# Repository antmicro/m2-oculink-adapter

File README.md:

# M.2 to OCuLink Adapter

Copyright (c) 2025 [Antmicro](https://www.antmicro.com)

## Overview

This project includes PCB design files that define a simple M.2 (M-key) to OCuLink adapter.
It can be used for connecting the on-board PCIe M.2 slots with remote PCIe devices via OCuLink cables. 
This board has been designed to be compatible with Antmicro's [Jetson Orin Baseboard](https://github.com/antmicro/jetson-orin-baseboard).

If you plan to use it with other pieces of hardware, please inspect the schematics and connection diagrams beforehand. 
The PCB design files were prepared in KiCad 9.x.

## Key features

- Compatible with Antmicro's Jetson Orin Baseboard
- Exposes 4 lanes of PCIe via an OCuLink connector
- M.2 (M-key)
- OCuLink connector (Amphenol G14A421211112HR)
- Compatible with 2280, 2260, 2242 M.2 mechanical form factors

## License

This project is licensed under the [Apache-2.0](LICENSE) license.

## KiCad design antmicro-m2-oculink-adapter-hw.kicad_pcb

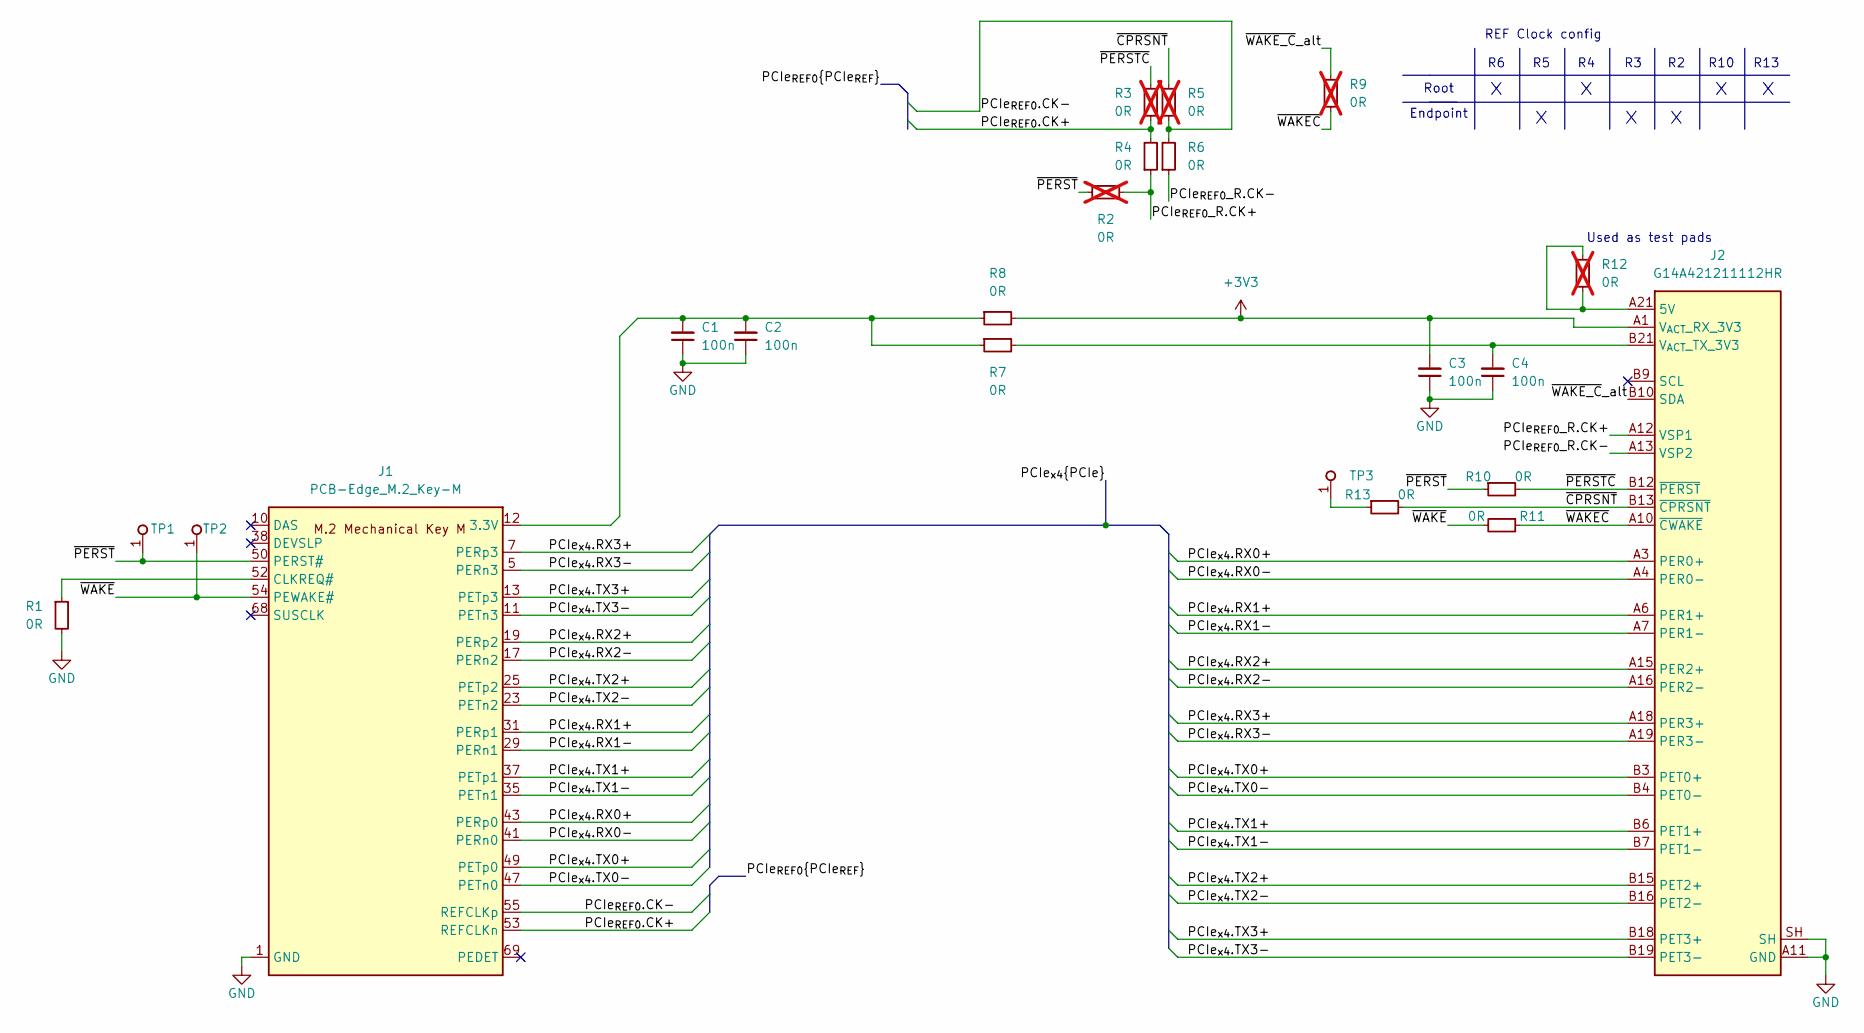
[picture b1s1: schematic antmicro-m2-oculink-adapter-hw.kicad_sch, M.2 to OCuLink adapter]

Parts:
C1, C2, C3, C4: C_100n_16V_X7R_0402; C_0402_1005Metric; Voltage 16V; MPN C0402C104J4RAC7411
J1: PCB-Edge_M.2_Key-M
J2: OCuLink_x4_Amphenol_G14A421211112HR; Amphenol_G14A421211112HR; MPN G14A421211112HR
R1, R7, R8, R11: R_0R_0402; R_0402_1005Metric; MPN ERJ2GE0R00X
R2, R3, R5, R9: R_0R_0201; R_0201; Tolerance 1%; MPN CR0201-FX-0R00GLF; not fitted
R4, R6, R10, R13: R_0R_0201; R_0201; Tolerance 1%; MPN CR0201-FX-0R00GLF
R12: R_0R_0402; R_0402_1005Metric; MPN ERJ2GE0R00X; not fitted
TP1, TP2: TP_1.5mm_SMD; TP_SMD_1.5mm
TP3: TP_1mm_SMD; TP_SMD_1mm

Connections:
+3V3: C3.2, J2.A1 (V_{ACT}_RX_3V3), R8.2
/PCIe_{REF0}.CK+: J1.53 (REFCLKn), R3.1, R4.2
/PCIe_{REF0}.CK-: J1.55 (REFCLKp), R5.1, R6.2
/PCIe_{REF0}_R.CK+: J2.A12 (VSP1), R2.1, R4.1
/PCIe_{REF0}_R.CK-: J2.A13 (VSP2), R6.1
/PCIe_{x4}.RX0+: J1.43 (PERp0), J2.A3 (PER0+)
/PCIe_{x4}.RX0-: J1.41 (PERn0), J2.A4 (PER0-)
/PCIe_{x4}.RX1+: J1.31 (PERp1), J2.A6 (PER1+)
/PCIe_{x4}.RX1-: J1.29 (PERn1), J2.A7 (PER1-)
/PCIe_{x4}.RX2+: J1.19 (PERp2), J2.A15 (PER2+)
/PCIe_{x4}.RX2-: J1.17 (PERn2), J2.A16 (PER2-)
/PCIe_{x4}.RX3+: J1.7 (PERp3), J2.A18 (PER3+)
/PCIe_{x4}.RX3-: J1.5 (PERn3), J2.A19 (PER3-)
/PCIe_{x4}.TX0+: J1.49 (PETp0), J2.B3 (PET0+)
/PCIe_{x4}.TX0-: J1.47 (PETn0), J2.B4 (PET0-)
/PCIe_{x4}.TX1+: J1.37 (PETp1), J2.B6 (PET1+)
/PCIe_{x4}.TX1-: J1.35 (PETn1), J2.B7 (PET1-)
/PCIe_{x4}.TX2+: J1.25 (PETp2), J2.B15 (PET2+)
/PCIe_{x4}.TX2-: J1.23 (PETn2), J2.B16 (PET2-)
/PCIe_{x4}.TX3+: J1.13 (PETp3), J2.B18 (PET3+)
/PCIe_{x4}.TX3-: J1.11 (PETn3), J2.B19 (PET3-)
/~CPRSNT: J2.B13 (~CPRSNT), R5.2, R13.2
/~PERSTC: J2.B12 (~PERST), R3.2, R10.2
/~PERST: J1.50 (PERST#), R2.2, R10.1, TP1.1
/~WAKEC: J2.A10 (~CWAKE), R9.1, R11.1
/~WAKE_C_alt: J2.B10 (SDA), R9.2
/~WAKE: J1.54 (PEWAKE#), R11.2, TP2.1
GND: C1.1, C2.1, C3.1, C4.1, J1.1 (GND), J1.3 (GND), J1.9 (GND), J1.15 (GND), J1.21 (GND), J1.27 (GND), J1.33 (GND), J1.39 (GND), J1.45 (GND), J1.51 (GND), J1.57 (GND), J1.71 (GND), J1.73 (GND), J1.75 (GND), J2.A2 (GND), J2.A5 (GND), J2.A8 (GND), J2.A11 (GND), J2.A14 (GND), J2.A17 (GND), J2.A20 (GND), J2.B2 (GND), J2.B5 (GND), J2.B8 (GND), J2.B11 (GND), J2.B14 (GND), J2.B17 (GND), J2.B20 (GND), J2.SH, R1.2
unnamed: C1.2, C2.2, J1.2 (3.3V), J1.4 (3.3V), J1.12 (3.3V), J1.14 (3.3V), J1.16 (3.3V), J1.18 (3.3V), J1.70 (3.3V), J1.72 (3.3V), J1.74 (3.3V), R7.1, R8.1
unnamed: J1.52 (CLKREQ#), R1.1
unnamed: J2.A21 (5V), J2.B1 (5V), R12.1, R12.2
unnamed: C4.2, J2.B21 (V_{ACT}_TX_3V3), R7.2
unnamed: R13.1, TP3.1

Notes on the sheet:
REF Clock config
Endpoint
Root
Used as test pads
R13
R10

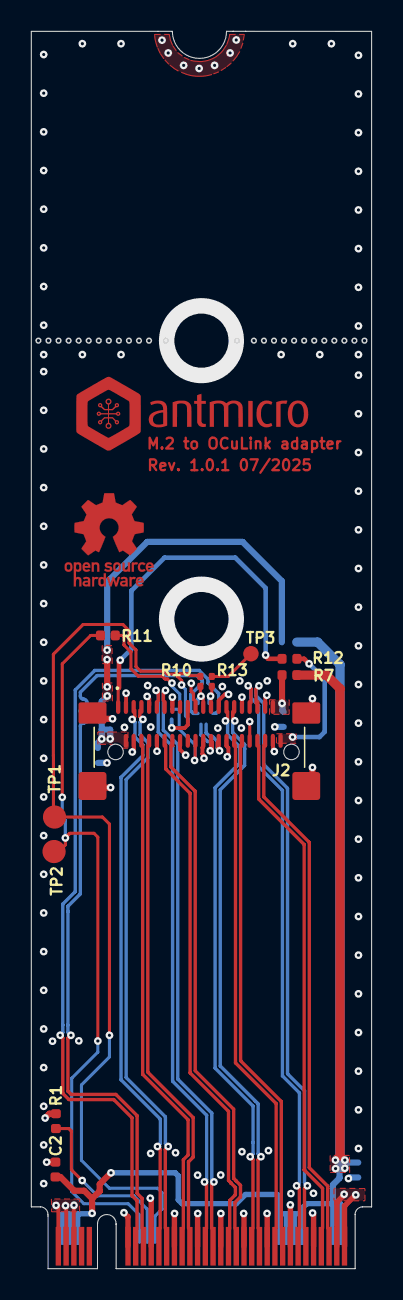
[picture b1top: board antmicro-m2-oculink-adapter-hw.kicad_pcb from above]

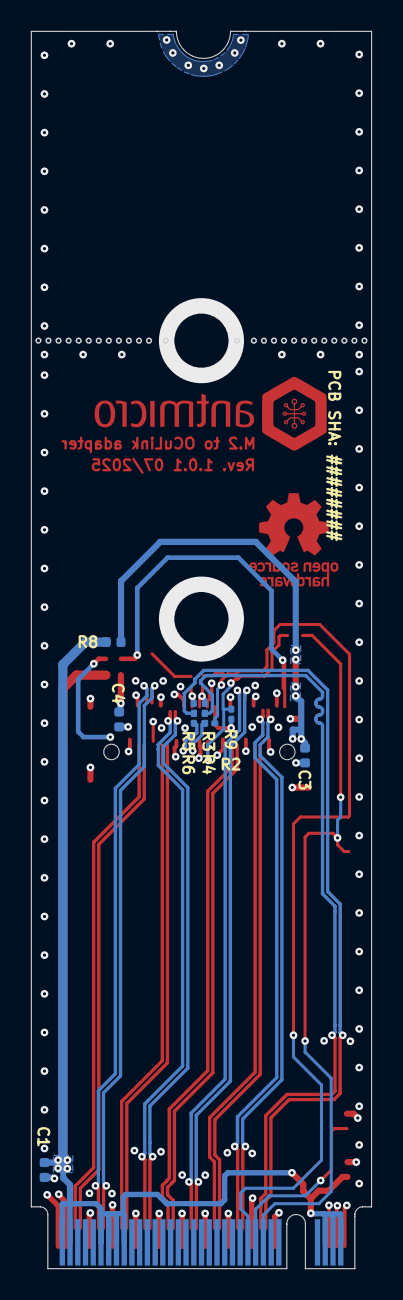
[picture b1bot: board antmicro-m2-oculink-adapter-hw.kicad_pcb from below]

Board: 4 copper layers, 22.0 x 80.0 mm, 22 parts (10 on the bottom side), 33 nets.

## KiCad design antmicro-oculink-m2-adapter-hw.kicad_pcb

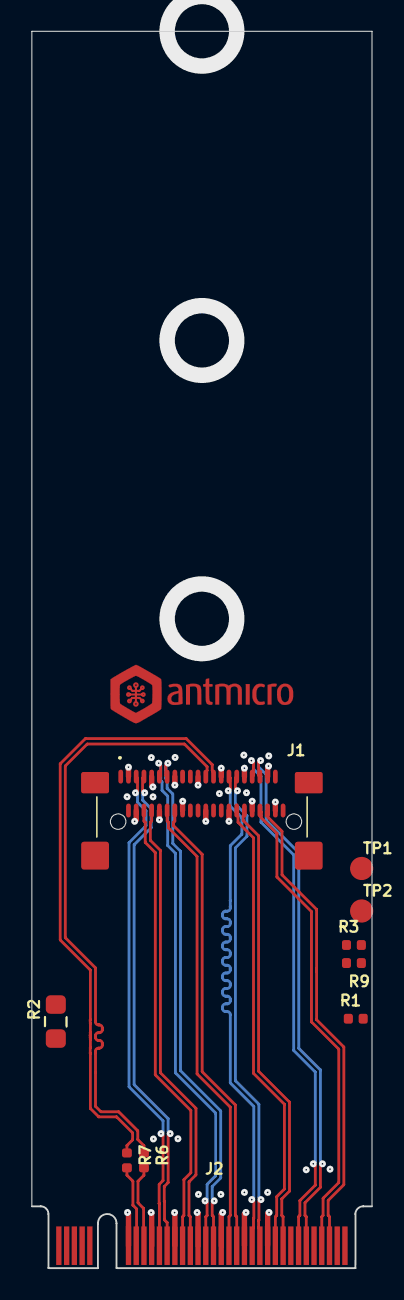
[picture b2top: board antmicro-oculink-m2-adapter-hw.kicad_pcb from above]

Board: 4 copper layers, 22.0 x 80.0 mm, 10 parts (0 on the bottom side), 28 nets.

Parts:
J1: OCuLink_x4_Amphenol_G14A421211112HR; Amphenol_G14A421211112HR
J2: PCB-Edge_M.2_Key-M
R1, R3, R6, R7, R9: R_0R_0402; R_0402_1005Metric
R2: R_0R_0805; R_0805_2012Metric
TP1, TP2: TP_1.5mm_SMD; TP_SMD_1.5mm

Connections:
+3V3: J1.A21 (V_{ACT}_TX_3V3), J1.B1 (V_{ACT}_RX_3V3), R2.2
/PCIe_{REF0}.CK+: J2.55 (REFCLKp), R7.2
/PCIe_{REF0}.CK-: J2.53 (REFCLKn), R6.2
/PCIe_{REF0}_R.CK+: J1.B13 (VSP2), R7.1
/PCIe_{REF0}_R.CK-: J1.B12 (VSP1), R6.1
/PCIe_{x4}.RX0+: J1.B3 (PER0+), J2.49 (SATA-A+)
/PCIe_{x4}.RX0-: J1.B4 (PER0-), J2.47 (SATA-A-)
/PCIe_{x4}.RX1+: J1.B6 (PER1+), J2.37 (PETp1)
/PCIe_{x4}.RX1-: J1.B7 (PER1-), J2.35 (PETn1)
/PCIe_{x4}.RX2+: J1.B15 (PER2+), J2.25 (PETp2)
/PCIe_{x4}.RX2-: J1.B16 (PER2-), J2.23 (PETn2)
/PCIe_{x4}.RX3+: J1.B18 (PER3+), J2.13 (PETp3)
/PCIe_{x4}.RX3-: J1.B19 (PER3-), J2.11 (PETn3)
/PCIe_{x4}.TX0+: J1.A3 (PET0+), J2.43 (SATA-B+)
/PCIe_{x4}.TX0-: J1.A4 (PET0-), J2.41 (SATA-B-)
/PCIe_{x4}.TX1+: J1.A6 (PET1+), J2.31 (PERp1)
/PCIe_{x4}.TX1-: J1.A7 (PET1-), J2.29 (PERn1)
/PCIe_{x4}.TX2+: J1.A15 (PET2+), J2.19 (PERp2)
/PCIe_{x4}.TX2-: J1.A16 (PET2-), J2.17 (PERn2)
/PCIe_{x4}.TX3+: J1.A18 (PET3+), J2.7 (PERp3)
/PCIe_{x4}.TX3-: J1.A19 (PET3-), J2.5 (PERn3)
/~PERSTC: J1.A12 (~PERST), R1.1
/~PERST: J2.50 (PERST#), R1.2, TP1.1
/~WAKEC: J1.B10 (~CWAKE), R3.1
/~WAKE: J2.54 (PEWAKE#), R3.2, TP2.1
GND: J1.A2 (GND), J1.A5 (GND), J1.A8 (GND), J1.A11 (GND), J1.A14 (GND), J1.A17 (GND), J1.A20 (GND), J1.B2 (GND), J1.B5 (GND), J1.B8 (GND), J1.B11 (GND), J1.B14 (GND), J1.B17 (GND), J1.B20 (GND), J1.SH, J2.1 (GND), J2.3 (GND), J2.9 (GND), J2.15 (GND), J2.21 (GND), J2.27 (GND), J2.33 (GND), J2.39 (GND), J2.45 (GND), J2.51 (GND), J2.57 (GND), J2.71 (GND), J2.73 (GND), J2.75 (GND), R9.2
unnamed: J2.2 (3.3V), J2.4 (3.3V), J2.12 (3.3V), J2.14 (3.3V), J2.16 (3.3V), J2.18 (3.3V), J2.70 (3.3V), J2.72 (3.3V), J2.74 (3.3V), R2.1
unnamed: J2.52 (CLKREQ#), R9.1

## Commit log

2025-07-09 [#79281] Inital commit
2025-07-24 [#80280] Add LICENSE
2025-07-24 [#79281] Update key features in README
2025-07-24 [#79281] add README.md
2025-07-24 [#79281] Add ci.yml, initial connector placement
2025-07-24 [#79281] Connector placement and PCIe routing
2025-07-24 [#79281] Add .gitignore and remove kicad_prl file
2025-07-24 [#79281] Remove unnecessary text on schematic
2025-07-24 [#79281] Fix lane polarity
2025-07-24 [#79281] Clean up gnd vias and pcie routing
2025-07-24 [#79281] Rename files, Fix net class naming, Undo crossover on PCIe lanes, change OCulink symbol to host side version
2025-07-24 [#79281] Remove old files
2025-07-24 [#79281] Place 0R resistors and test points
2025-07-24 [#80280] Add mouse bites
2025-07-24 [#79281] Fix schematic annotation
2025-07-24 [#79281] Change 0R sizing, add OSHW logo, route 3.3V rail and control signals
2025-07-24 [#80280] Fix DRC
2025-07-24 [#80280] Round diff pairs. Move logo to 2 segment and make more room for the OCulink cable
2025-07-24 [#80280] CI test
2025-07-24 [#80280] Add PCB SHA string
2025-07-24 [#80280] Move edge cuts from footprints
2025-07-24 [#80280] Workaround kicad bug
2025-07-24 [#80280] Modify edge drill hole to use pad instead of filled polygon
2025-07-24 [#80280] Rename edge drill hole, fix drc
2025-07-24 [#80280] Add User 9 layer
2025-07-24 [#80280] Clean up tracks, change gnd cutout size, fix drc errors, add more vias, move antmicro logo, change text size
2025-07-24 [#80280] Cleanup tracks
2025-07-24 [#80747] Add license info to README
2025-07-24 [#80747] Add render to README
2025-07-24 [#80747] Update testpoint info in README
2025-07-24 [#80747] Clean up tracks
2025-07-24 [#80747] change antmicro logo and correct date format
2025-07-24 [#80747] Fix DRC
2025-07-24 [#80747] Replace edge drill footprint
2025-07-24 [#80747] Kmake bug workaround
2025-07-24 [#80747] Update README
2025-07-24 [#80747] Remove soldermask from drill opening
2025-07-24 [#80747] Update render
2025-07-24 [#80747] Change drill hole size to 3.5mm
2025-07-24 README: update description, resize render
2025-07-24 README: Fix name
2025-07-24 minor text refinement
2025-07-24 further language review
2025-07-24 minor fixes
2025-07-24 the ceremonial unification of the M-key
2025-07-25 [#80997] Fix stack-up
2025-07-28 [#81030] Rotate sha
2025-07-28 [#81030] Change OCulink connector pad size to 0.28mm
2025-07-31 [#81131] Change resistor, testpoint sizing. Add 0R to 3V3 and ~CWAKE
2025-07-31 [#81131] Add 0R selector for refclk
2025-07-31 [#81131] Cleanup tracks
2025-07-31 [#81131] Clean up drc
2025-07-31 [#81131] Fix meander add gnd connections
2025-07-31 [#81131] Fix vias, zones
2025-07-31 [#81131] Fix schematic 3V3
2025-07-31 [#81131] Clean drc
2025-07-31 [#81131] Clean-up tracks, shorten stubs, relocate R1, align silkscreen
2025-07-31 [#81131] Add 0R on 5V, Clean drc
2025-08-01 [#81131] Increase silkscreen spacing, add gnd cutouts to vias, increase distance drill to traces, remove solder mask from m.2 connector
2025-08-01 [#81131] remove silkscreen from revision, add testpoint to CPRSNT
2025-08-01 [#81131] Kmake bug workaround
2025-08-01 [#81131] Remove plane, adjust silkscreen
2025-08-01 [#81131] Align silkscreen
2025-08-12 [#81086] Change mousebite size to 0.4mm diameter
2025-08-14 [#81086] Remove unnecesary GND cutout, bump revision

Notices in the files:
parts and their libraries:
License: Apache-2.0
